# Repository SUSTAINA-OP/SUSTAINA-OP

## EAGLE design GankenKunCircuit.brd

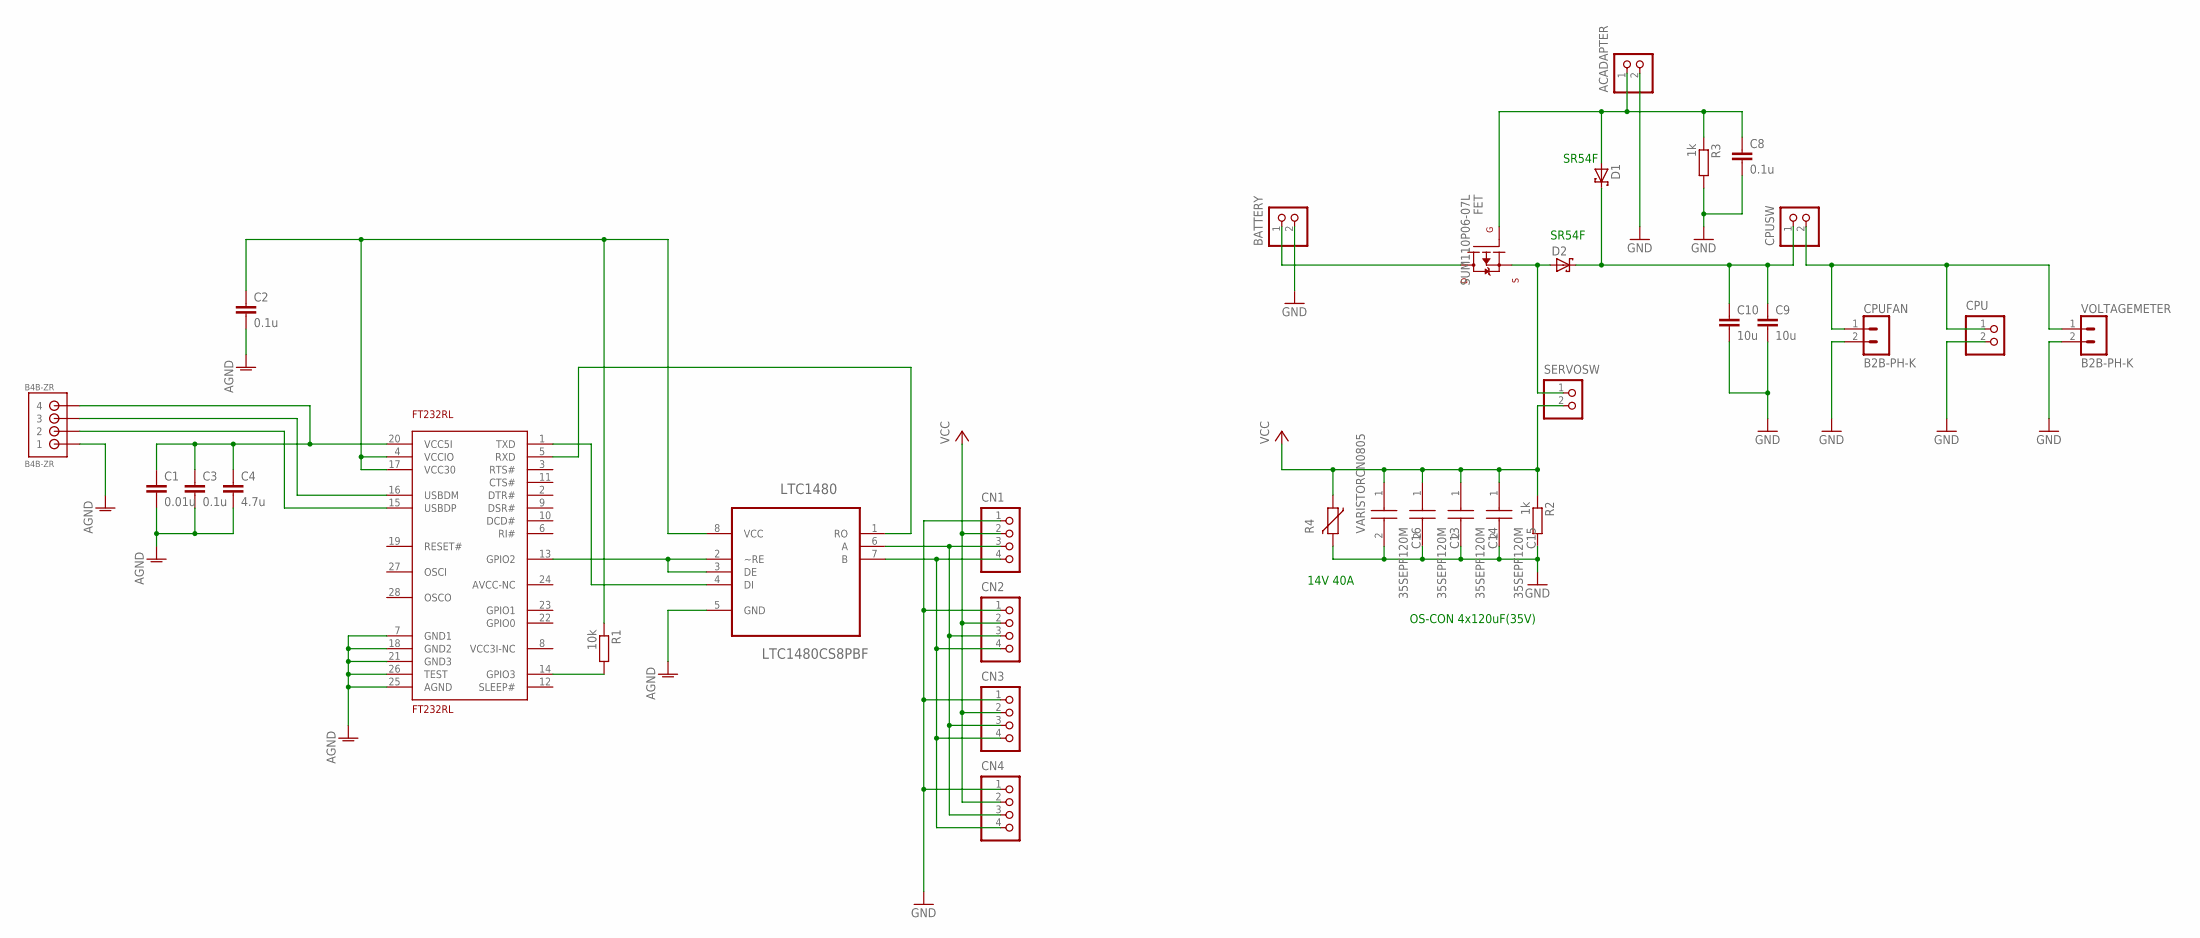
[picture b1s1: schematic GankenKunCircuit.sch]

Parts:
ACADAPTER: B2B-XH-A
B4B-ZR: B4B-ZR
BATTERY: B2P-VH
C1: 0.01u; C2012
C2, C3, C8: 0.1u; C2012
C4: 4.7u; C2012
C9, C10: 10u; C3216
C13, C14, C15, C16: 35SEPF120M; CAPPRD500W65D1000H1350
CN1, CN2, CN3, CN4: B4B-XH-A
CPU: B2B-XH-A
CPUFAN: B2B-PH-K
CPUSW: B2B-XH-A
D1, D2: SCHOTTKY-DIODESMD; SMB
FET: SUM110P06-07L; TO-263-2
FT232RL: FT232RL; SSOP28
LTC1480: LTC1480CS8PBF; SOIC127P600X175-8N
R1: 10k; M2012
R2, R3: 1k; M2012
R4: VARISTORCN0805; CT/CN0805
SERVOSW: B2P-VH
VOLTAGEMETER: B2B-PH-K

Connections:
AGND: B4B-ZR.1, C1.2, C2.2, C3.2, C4.2, FT232RL.7 (GND1), FT232RL.18 (GND2), FT232RL.21 (GND3), FT232RL.25 (AGND), FT232RL.26 (TEST), LTC1480.5 (GND)
GND: ACADAPTER.2, BATTERY.2, C8.2, C9.2, C10.2, C13.2 (-), C14.2 (-), C15.2 (-), C16.2 (-), CN1.1, CN2.1, CN3.1, CN4.1, CPU.2, CPUFAN.2, R2.2, R3.2, R4.2, VOLTAGEMETER.2
unnamed: C2.1, FT232RL.4 (VCCIO), FT232RL.17 (VCC30), LTC1480.8 (VCC), R1.1
unnamed: B4B-ZR.4, C1.1, C3.1, C4.1, FT232RL.20 (VCC5I)
unnamed: FT232RL.14 (GPIO3), R1.2
unnamed: B4B-ZR.3, FT232RL.16 (USBDM)
unnamed: B4B-ZR.2, FT232RL.15 (USBDP)
unnamed: CN1.4, CN2.4, CN3.4, CN4.4, LTC1480.7 (B)
unnamed: FT232RL.1 (TXD), LTC1480.4 (DI)
unnamed: FT232RL.5 (RXD), LTC1480.1 (RO)
unnamed: FT232RL.13 (GPIO2), LTC1480.2 (~RE), LTC1480.3 (DE)
unnamed: CN1.3, CN2.3, CN3.3, CN4.3, LTC1480.6 (A)
unnamed: BATTERY.1, FET.4 (D)
unnamed: D2.A, FET.3 (S), SERVOSW.1
unnamed: C9.1, C10.1, CPUSW.1, D1.C, D2.C
unnamed: ACADAPTER.1, C8.1, D1.A, FET.1 (G), R3.1
unnamed: CPU.1, CPUFAN.1, CPUSW.2, VOLTAGEMETER.1
VCC: C13.1 (+), C14.1 (+), C15.1 (+), C16.1 (+), CN1.2, CN2.2, CN3.2, CN4.2, R2.1, R4.1, SERVOSW.2

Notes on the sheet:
14V 40A
SR54F
OS-CON 4x120uF(35V)

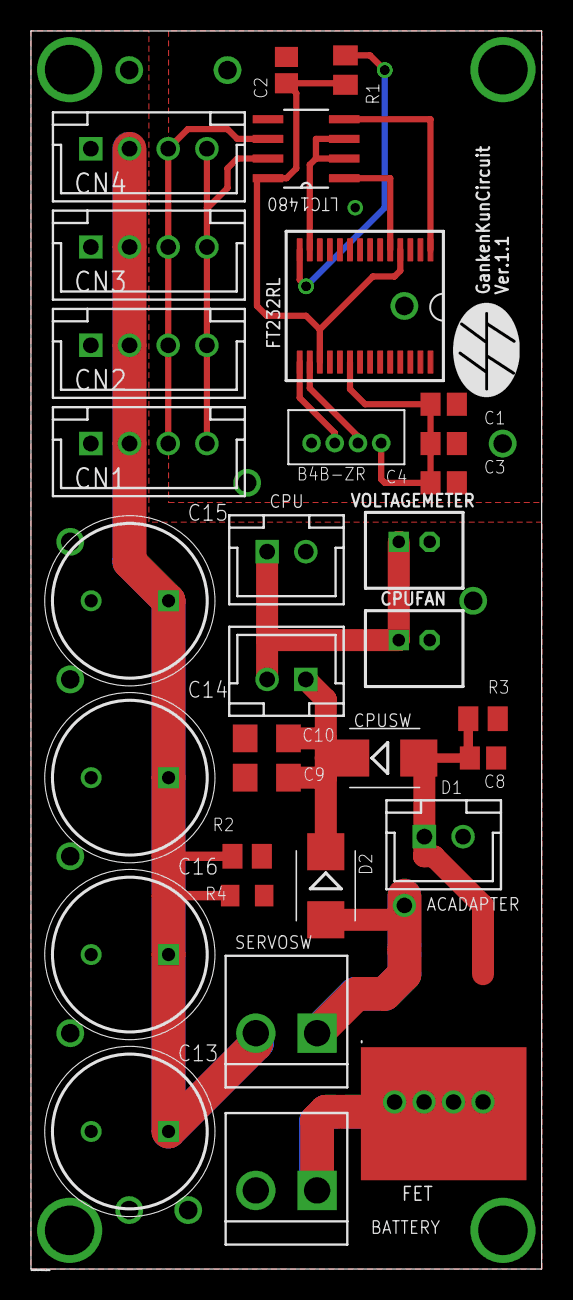
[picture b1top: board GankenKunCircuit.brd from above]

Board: 2 copper layers, 33.0 x 80.0 mm, 32 parts (0 on the bottom side), 18 nets.

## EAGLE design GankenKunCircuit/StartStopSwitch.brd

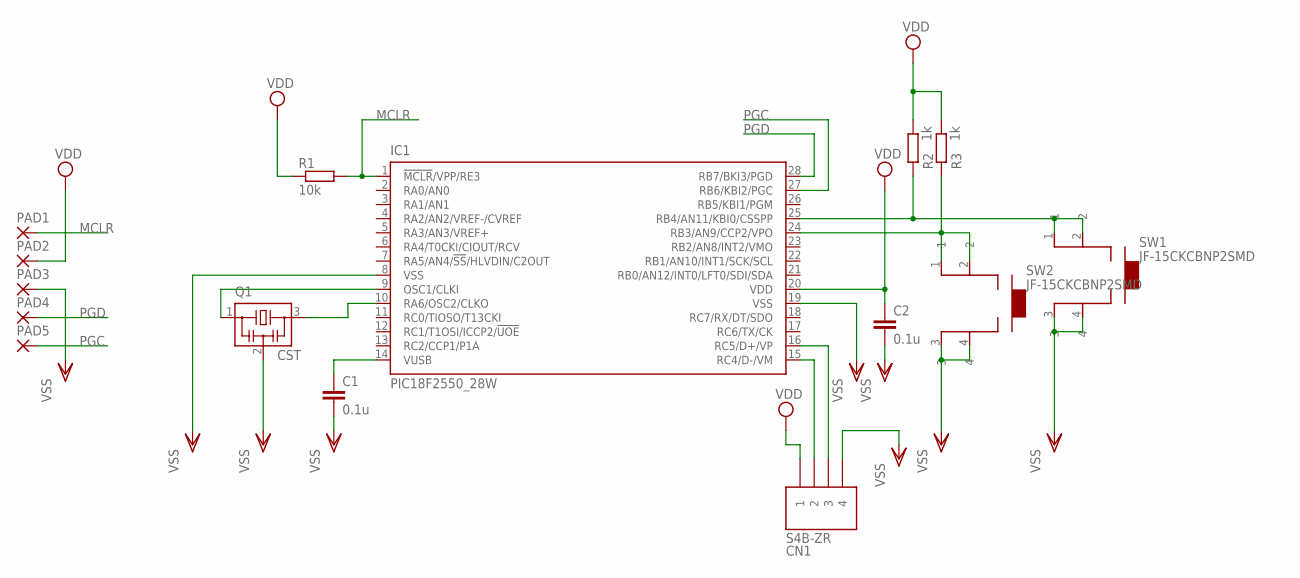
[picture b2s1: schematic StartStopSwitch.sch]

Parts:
C1, C2: 0.1u; C2012
CN1: S4B-ZR
IC1: PIC18F2550_28W; SO28W
PAD1, PAD2, PAD3, PAD4, PAD5: WIREPADSMD1,27-254; SMD1,27-2,54
Q1: CST; CSTCR6M-MINI
R1: 10k; R0805
R2, R3: 1k; R0805
SW1, SW2: JF-15CKCBNP2SMD; JF-15CKCBNP2-SMD

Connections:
24: IC1.24 (RB3/AN9/CCP2/VPO), R3.1, SW2.1, SW2.2
25: IC1.25 (RB4/AN11/KBI0/CSSPP), R2.1, SW1.1, SW1.2
D+: CN1.3, IC1.16 (RC5/D+/VP)
D-: CN1.2, IC1.15 (RC4/D-/VM)
MCLR: IC1.1 (!MCLR!/VPP/RE3), PAD1.1, R1.2
unnamed: C1.1, IC1.14 (VUSB)
unnamed: IC1.9 (OSC1/CLKI), Q1.1
unnamed: IC1.10 (RA6/OSC2/CLKO), Q1.3
PGC: IC1.27 (RB6/KBI2/PGC), PAD5.1
PGD: IC1.28 (RB7/BKI3/PGD), PAD4.1
VDD: C2.1, CN1.1, IC1.20 (VDD), PAD2.1, R1.1, R2.2, R3.2
VSS: C1.2, C2.2, CN1.4, IC1.8 (VSS), IC1.19 (VSS), PAD3.1, Q1.2, SW1.3, SW1.4, SW2.3, SW2.4

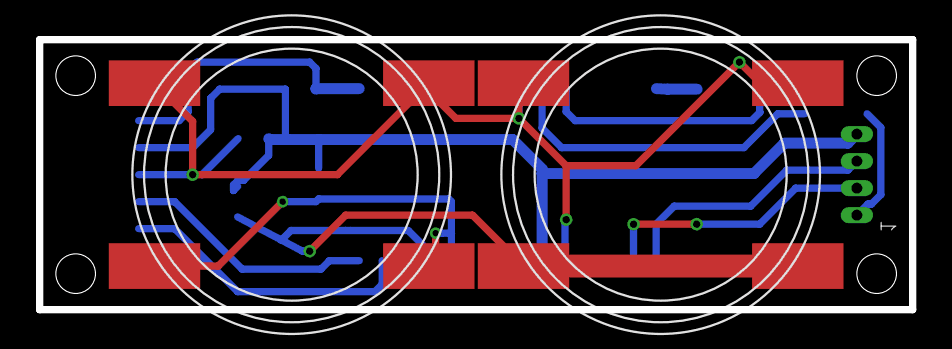
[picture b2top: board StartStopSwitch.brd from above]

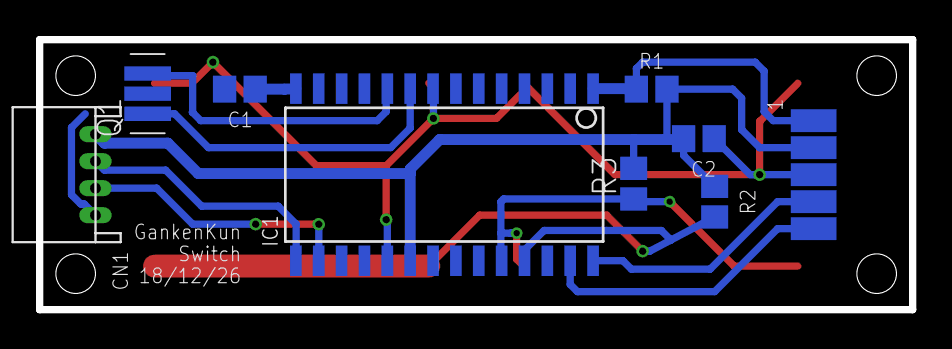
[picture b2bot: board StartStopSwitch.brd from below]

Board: 2 copper layers, 48.5 x 15.0 mm, 15 parts (13 on the bottom side), 12 nets.

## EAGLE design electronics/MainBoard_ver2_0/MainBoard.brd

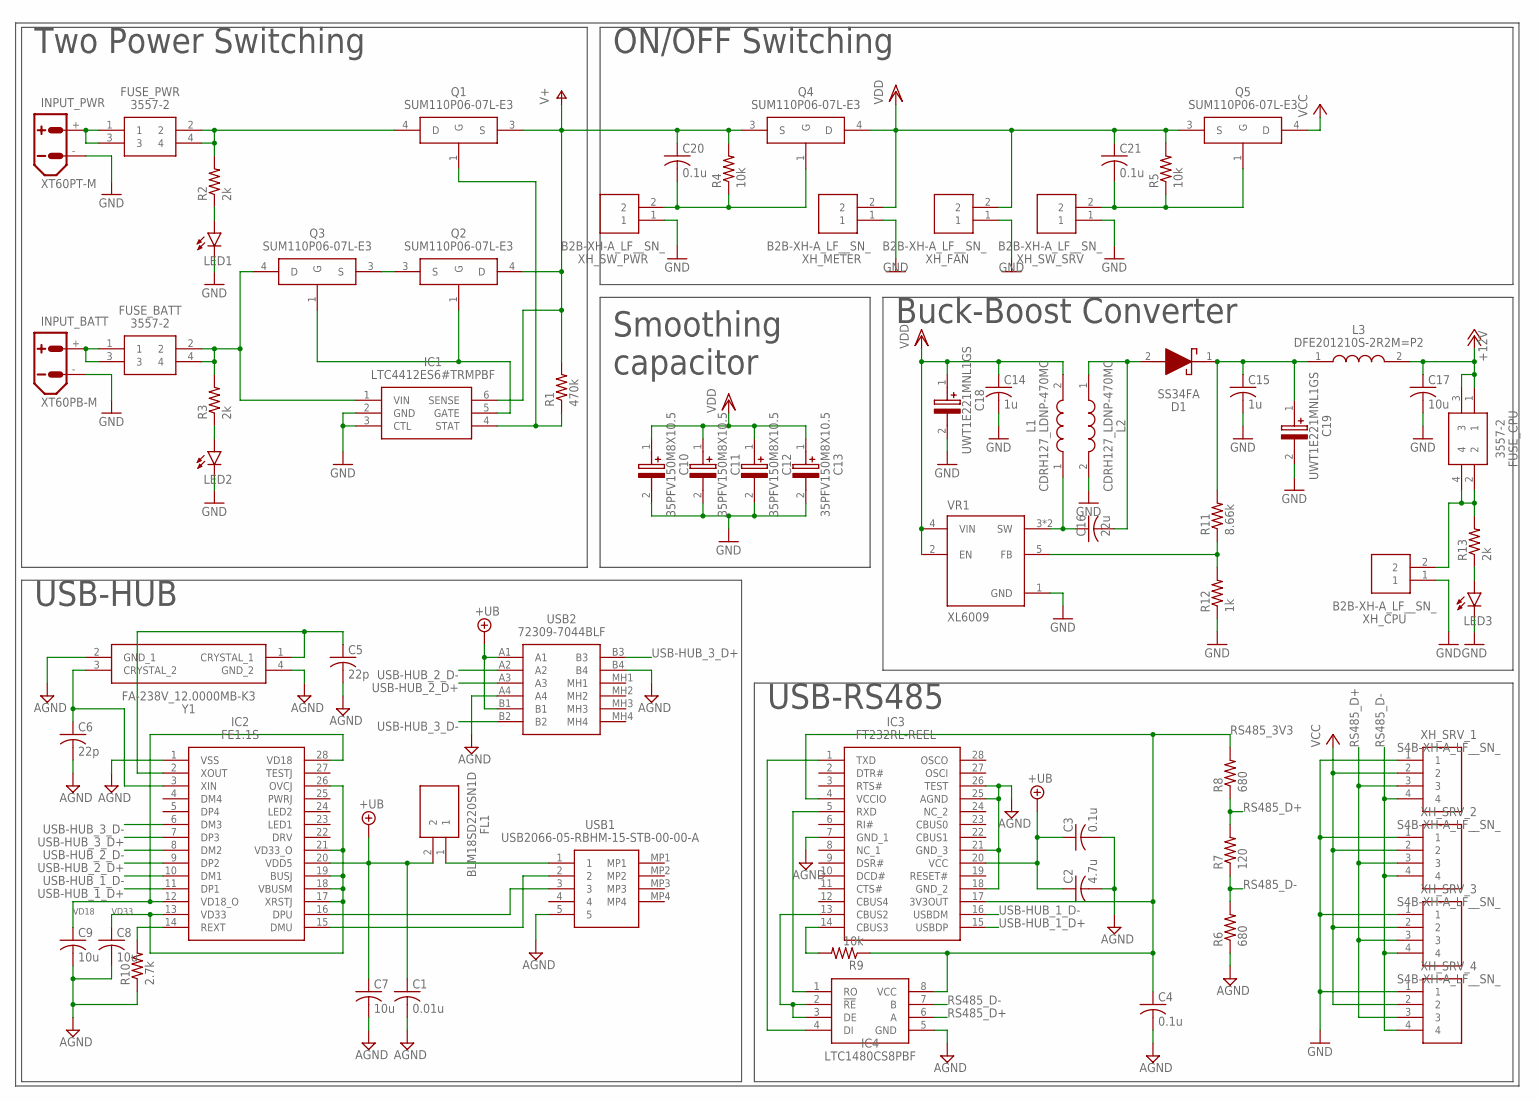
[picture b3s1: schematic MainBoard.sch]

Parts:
C1: 0.01u; C1608
C2: 4.7u; C1608
C3, C4, C20, C21: 0.1u; C1608
C5, C6: 22p; C1608
C7, C8, C9, C17: 10u; C1608
C10, C11, C12, C13: 35PFV150M8X10.5; CAPAE830X1050N
C14, C15: 1u; C1608
C16: 22u; C2012
C18, C19: UWT1E221MNL1GS; CAPAE830X1080N
D1: SS34FA; SODFL3618X143N
FL1: BLM18SD220SN1D; BLM18AG102BH1D
FUSE_BATT: 3557-2
FUSE_CPU: 3557-2
FUSE_PWR: 3557-2
IC1: LTC4412ES6#TRMPBF; SOT95P280X100-6N
IC2: FE1.1S; SOP64P600X175-28N
IC3: FT232RL-REEL; SOP65P778X200-28N
IC4: LTC1480CS8PBF; SOIC127P599X175-8N
INPUT_BATT: XT60PB-M
INPUT_PWR: XT60PT-M
L1, L2: CDRH127_LDNP-470MC; INDPM120120X800N
L3: DFE201210S-2R2M=P2; DFE201210S1R0MP2
LED1, LED2, LED3: LEDSML0603; SML0603
Q1, Q2, Q3, Q4, Q5: SUM110P06-07L-E3; TO254P1524X483-4N
R1: 470k; R0603
R2, R3, R13: 2k; R0603
R4, R5, R9: 10k; R0603
R6, R8: 680; R0603
R7: 120; R0603
R10: 2.7k; R0603
R11: 8.66k; R0603
R12: 1k; R0603
USB1: USB2066-05-RBHM-15-STB-00-00-A; USB206605RBHM15STB0000A
USB2: 72309-7044BLF; 723097044BLF
VR1: XL6009; DPAK170P1435X465-6N
XH_CPU: B2B-XH-A_LF__SN_; SHDR2W64P0X250_1X2_740X575X700
XH_FAN: B2B-XH-A_LF__SN_; SHDR2W64P0X250_1X2_740X575X700
XH_METER: B2B-XH-A_LF__SN_; SHDR2W64P0X250_1X2_740X575X700
XH_SRV_1, XH_SRV_2, XH_SRV_3, XH_SRV_4: S4B-XH-A_LF__SN_; SHDRRA4W64P0X250_1X4_1240X1150
XH_SW_PWR: B2B-XH-A_LF__SN_; SHDR2W64P0X250_1X2_740X575X700
XH_SW_SRV: B2B-XH-A_LF__SN_; SHDR2W64P0X250_1X2_740X575X700
Y1: FA-238V_12.0000MB-K3; FA238V120000MBK3

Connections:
+12V: C17.1, FUSE_CPU.1, FUSE_CPU.3, L3.2
+UB: C1.1, C2.1, C3.1, C7.1, FL1.2, IC2.20 (VDD5), IC3.20 (VCC), USB2.A1, USB2.B1
AFTER_FUSE_BATT: FUSE_BATT.2, FUSE_BATT.4, IC1.1 (VIN), Q3.4 (D), R3.2
AFTER_FUSE_CPU: FUSE_CPU.2, FUSE_CPU.4, R13.2, XH_CPU.2
AFTER_FUSE_PWR: FUSE_PWR.2, FUSE_PWR.4, Q1.4 (D), R2.2
AGND: C1.2, C2.2, C3.2, C4.2, C5.2, C6.2, C7.2, C8.2, C9.2, IC2.1 (VSS), IC3.7 (GND_1), IC3.18 (GND_2), IC3.21 (GND_3), IC3.25 (AGND), IC3.26 (TEST), IC4.5 (GND), R6.1, R10.1, USB1.5, USB2.A4, USB2.B4, Y1.2 (GND_1), Y1.4 (GND_2)
BEFORE_FUSE_BATT: FUSE_BATT.1, FUSE_BATT.3, INPUT_BATT.+
BEFORE_FUSE_PWR: FUSE_PWR.1, FUSE_PWR.3, INPUT_PWR.+
DCDC_1: C16.1, L1.1, VR1.3 (SW), VR1.6 (SW)
DCDC_2: C16.2, D1.2 (A), L2.1
DCDC_3: C15.1, C19.1 (+), D1.1 (K), L3.1, R11.2
DCDC_4: R11.1, R12.2, VR1.5 (FB)
FET_S_S: Q2.3 (S), Q3.3 (S)
GND: C10.2 (-), C11.2 (-), C12.2 (-), C13.2 (-), C14.2, C15.2, C17.2, C18.2 (-), C19.2 (-), IC1.2 (GND), IC1.3 (CTL), INPUT_BATT.-, INPUT_PWR.-, L2.2, LED1.C, LED2.C, LED3.C, R12.1, VR1.1 (GND), XH_CPU.1, XH_FAN.1, XH_METER.1, XH_SRV_1.1, XH_SRV_2.1, XH_SRV_3.1, XH_SRV_4.1, XH_SW_PWR.1, XH_SW_SRV.1
LED1: LED1.A, R2.1
LED2: LED2.A, R3.1
LED3: LED3.A, R13.1
unnamed: IC1.5 (GATE), Q2.1 (G), Q3.1 (G)
unnamed: C20.2, Q4.1 (G), R4.1, XH_SW_PWR.2
unnamed: C21.2, Q5.1 (G), R5.1, XH_SW_SRV.2
unnamed: C5.1, IC2.2 (XOUT), Y1.1 (CRYSTAL_1)
unnamed: FL1.1, USB1.1
unnamed: C6.1, IC2.3 (XIN), Y1.3 (CRYSTAL_2)
unnamed: IC2.15 (DMU), USB1.2
unnamed: IC2.16 (DPU), USB1.3
unnamed: IC2.14 (REXT), R10.2
POWER_SW1: IC1.4 (STAT), Q1.1 (G), R1.1
RS485_1: IC3.14 (CBUS3), R9.2
RS485_2: IC3.13 (CBUS2), IC4.2 (!RE), IC4.3 (DE)
RS485_3V3: C4.1, IC3.4 (VCCIO), IC3.17 (3V3OUT), IC4.8 (VCC), R8.2, R9.1
RS485_D+: IC4.6 (A), R7.2, R8.1, XH_SRV_1.3, XH_SRV_2.3, XH_SRV_3.3, XH_SRV_4.3
RS485_D-: IC4.7 (B), R6.2, R7.1, XH_SRV_1.4, XH_SRV_2.4, XH_SRV_3.4, XH_SRV_4.4
RXD: IC3.5 (RXD), IC4.1 (RO)
TXD: IC3.1 (TXD), IC4.4 (DI)
USB-HUB_1_D+: IC2.11 (DP1), IC3.15 (USBDP)
USB-HUB_1_D-: IC2.10 (DM1), IC3.16 (USBDM)
USB-HUB_2_D+: IC2.9 (DP2), USB2.A3
USB-HUB_2_D-: IC2.8 (DM2), USB2.A2
USB-HUB_3_D+: IC2.7 (DP3), USB2.B3
USB-HUB_3_D-: IC2.6 (DM3), USB2.B2
V+: C20.1, IC1.6 (SENSE), Q1.3 (S), Q2.4 (D), Q4.3 (S), R1.2, R4.2
VCC: Q5.4 (D), XH_SRV_1.2, XH_SRV_2.2, XH_SRV_3.2, XH_SRV_4.2
VD18: C9.1, IC2.12 (VD18_O), IC2.28 (VD18)
VD33: C8.1, IC2.13 (VD33), IC2.17 (XRSTJ), IC2.18 (VBUSM), IC2.19 (BUSJ), IC2.21 (VD33_O), IC2.26 (OVCJ)
VDD: C10.1 (+), C11.1 (+), C12.1 (+), C13.1 (+), C14.1, C18.1 (+), C21.1, L1.2, Q4.4 (D), Q5.3 (S), R5.2, VR1.2 (EN), VR1.4 (VIN), XH_FAN.2, XH_METER.2

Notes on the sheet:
ON/OFF Switching
Buck-Boost Converter
Two Power Switching
USB-RS485
USB-HUB
Smoothing capacitor

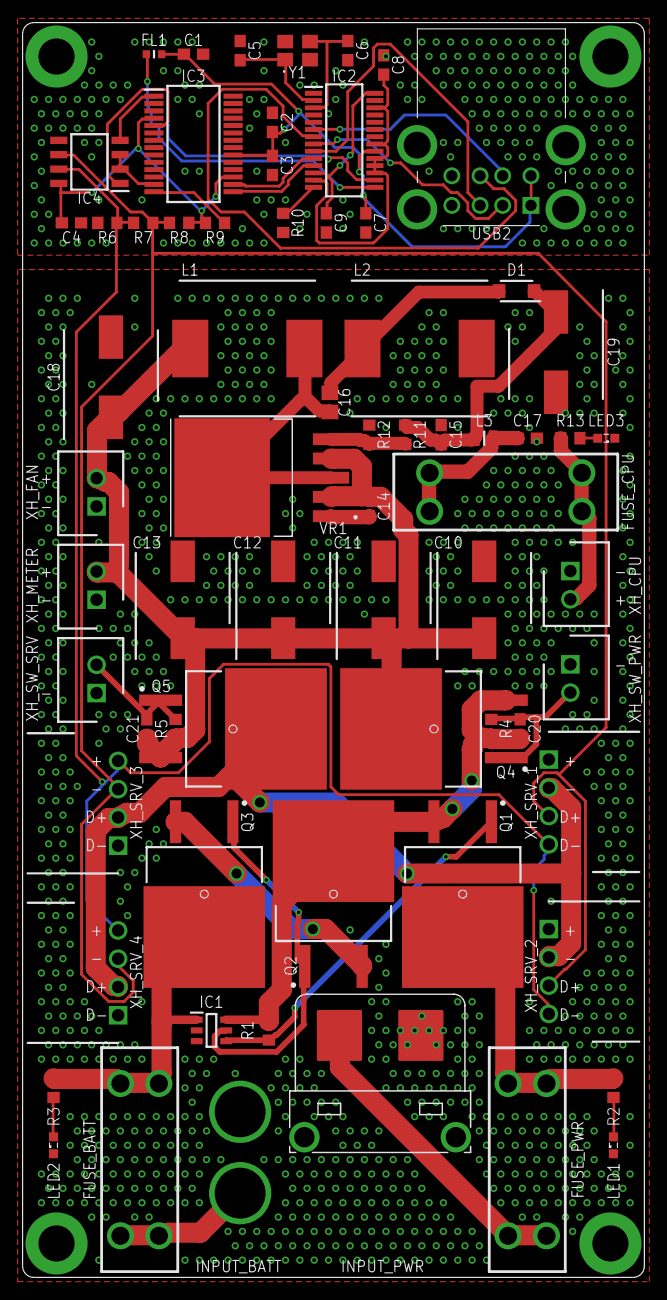
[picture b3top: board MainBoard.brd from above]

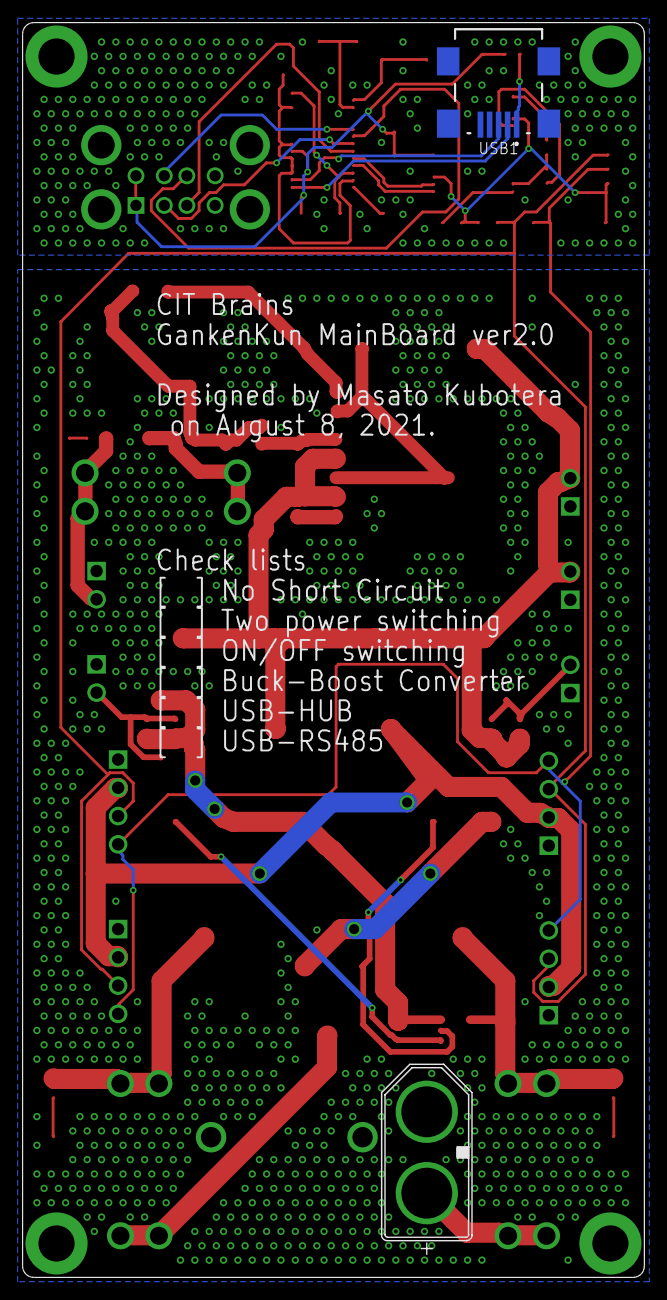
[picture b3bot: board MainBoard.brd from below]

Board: 2 copper layers, 55.0 x 111.0 mm, 69 parts (2 on the bottom side), 45 nets.

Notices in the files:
parts and their libraries:
jst-ph: Copyright (C) 2016, Bob Starr
SparkFun-PowerSymbols: Licensing: Creative Commons ShareAlike 4.0 International - https://creativecommons.org/licenses/by-sa/4.0
